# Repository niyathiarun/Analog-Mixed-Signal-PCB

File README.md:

# ⚙️ Analog–Mixed Signal PCB Project  

## 🧠 Project Overview  
This project focuses on designing and implementing a **mixed-signal printed circuit board (PCB)** that integrates both **analog** and **digital** subsystems on a single platform.  
The design features an **ATmega8L microcontroller** as the digital processing unit and an **operational amplifier (Op-Amp)** for analog signal conditioning.  

This project demonstrates key aspects of **analog–digital interfacing**, **signal conditioning**, **noise isolation**, and **mixed-signal PCB design principles**.  
All schematics, layouts, and fabrication outputs were created using **KiCad EDA**.

---

## 🎯 Objectives  

- To design and simulate a **mixed-signal circuit** combining analog and digital components.  
- To interface an **Op-Amp**-based analog conditioning circuit with a **microcontroller ADC**.  
- To implement effective **ground separation and power filtering** for signal integrity.  
- To generate **Gerber and drill files** for PCB fabrication and validation.  
- To gain hands-on experience in **mixed-signal design workflow** using KiCad.  

---

## 🧩 Key Features  

- **Microcontroller:** ATmega8L-8A (8-bit AVR MCU operating at 8 MHz)  
- **Analog Section:** Op-Amp-based amplifier and filter network  
- **Power Section:** 5V regulated supply with decoupling capacitors and ferrite bead  
- **Ground Planes:** Independent **GNDA** (Analog Ground) and **GNDD** (Digital Ground)  
- **Signal Interface:** Audio connector for analog input/output  
- **Design Tool:** KiCad 9.0.3  
- **Layers:** Two-layer PCB  
- **Fabrication Output:** Gerber and Drill files ready for manufacturing  

---

## 🧠 Circuit Explanation  

### 🔸 1. ATmega8L Microcontroller Section  
- Serves as the **digital control and processing unit**.  
- Reads analog signals from the op-amp through its **ADC pins**.  
- Capable of further processing, control, or display applications.  
- Decoupling capacitors are placed near **VCC** and **AVCC** pins to ensure stable ADC readings.  

### 🔸 2. Op-Amp Signal Conditioning Section  
- Amplifies and filters analog signals before feeding them into the ADC.  
- Provides clean and accurate analog voltages for digital conversion.  
- Includes RC filtering for stability and noise suppression.  
- Powered by the same 5V line as the MCU, isolated using ferrite bead and bypass capacitors.  

### 🔸 3. Power & Ground Separation  
- Power input through a **5V regulated line**.  
- **Ferrite bead** isolates analog and digital power domains.  
- **GNDA** and **GNDD** connected through a single low-impedance point near the power input.  
- This reduces cross-domain noise coupling and ensures better ADC accuracy.  

---

## 📐 PCB Design Highlights  

| Aspect | Description |
|--------|--------------|
| **Board Type** | 2-layer PCB |
| **Track Width** | Optimized based on current requirements |
| **Via Usage** | Minimal, used only for signal transitions |
| **Placement** | Clear separation between analog and digital components |
| **Ground Strategy** | Split ground plane with a single-star connection |
| **Decoupling** | 0.1µF ceramic + 10µF electrolytic capacitors near power pins |
| **Design Checks** | Passed ERC and DRC validation in KiCad |

---

## 📂 Repository Structure  

Analog-Mixed-Signal-PCB/
│
├── Schematic/
│ └── mixed_signal_project.kicad_sch
├── schematic_preview.png
│
├── PCB_Design/
│ └── mixed_signal_project.kicad_pcb
│ └── pcb_layout.png
│
├── Fabrication_Files/
│ ├── Gerber/
│ └── Drill_Files/
│ └── Gerber_drill_layout.png
│
└── README.md

---

## 🧰 Tools and Components  

| Category | Details |
|-----------|----------|
| **EDA Software** | KiCad 9.0.3 |
| **Microcontroller** | ATmega8L-8A |
| **Operational Amplifier** | LM358 / LM741 |
| **Power Source** | 5V DC Regulated Input |
| **Passive Components** | Resistors, capacitors, ferrite bead |
| **Connector** | Audio Jack (Analog I/O) |
| **Capacitors** | 0.1µF (decoupling), 10µF (filtering) |

---

## ⚡ Fabrication Notes  

- **Track Width:** 0.25 mm  
- **Clearance:** 0.2 mm  
- **Hole Diameter:** 0.8 mm  
- **Silkscreen:** Includes all reference designators and pin numbers  
- **Gerber Verification:** Done using Gerber Viewer before upload  
- **Board Type:** Standard FR-4 substrate, 1.6 mm thickness  

---

## 📈 Design Validation  

- ✅ **ERC (Electrical Rules Check):** No unconnected or shorted nets  
- ✅ **DRC (Design Rules Check):** Fully passed in KiCad  
- ✅ **Gerber Verification:** Verified visually for alignment and polarity   

---

## 🧩 Applications  

This mixed-signal PCB design has a wide range of **educational and industrial applications**, such as:  

- 🎛️ **Sensor Interface Systems** – conditioning analog sensor outputs before ADC conversion.  
- 🎚️ **Data Acquisition Systems** – capturing analog signals for processing in microcontrollers.  
- 🔊 **Audio Signal Processing** – amplifying and filtering low-level audio inputs.  
- 🧮 **Embedded Control Units** – combining analog feedback with digital decision logic.  
- 🧠 **Learning Platform** – for understanding mixed-signal PCB layout techniques.  

---

## 🧩 Learning Outcomes  

- Designed a **mixed-signal circuit** with analog–digital coexistence.  
- Implemented **noise isolation** and **power decoupling** techniques.  
- Created a **fabrication-ready PCB** with Gerber and drill files.  
- Practiced **KiCad design workflow** — schematic → layout → Gerber.  
- Gained insight into **real-world PCB manufacturing constraints**.  

---

## 🧑‍💻 Author  

**Niyathi Arun Kurthkoti**  
🎓 Electronics and Communication Engineering Student  
💡 Enthusiastic about Embedded Systems, PCB Design, and IoT  
📍 Passionate about creating real-world hardware solutions  

📫 *Connect with me:*  
[🔗 LinkedIn](www.linkedin.com/in/niyathiarun) 

---

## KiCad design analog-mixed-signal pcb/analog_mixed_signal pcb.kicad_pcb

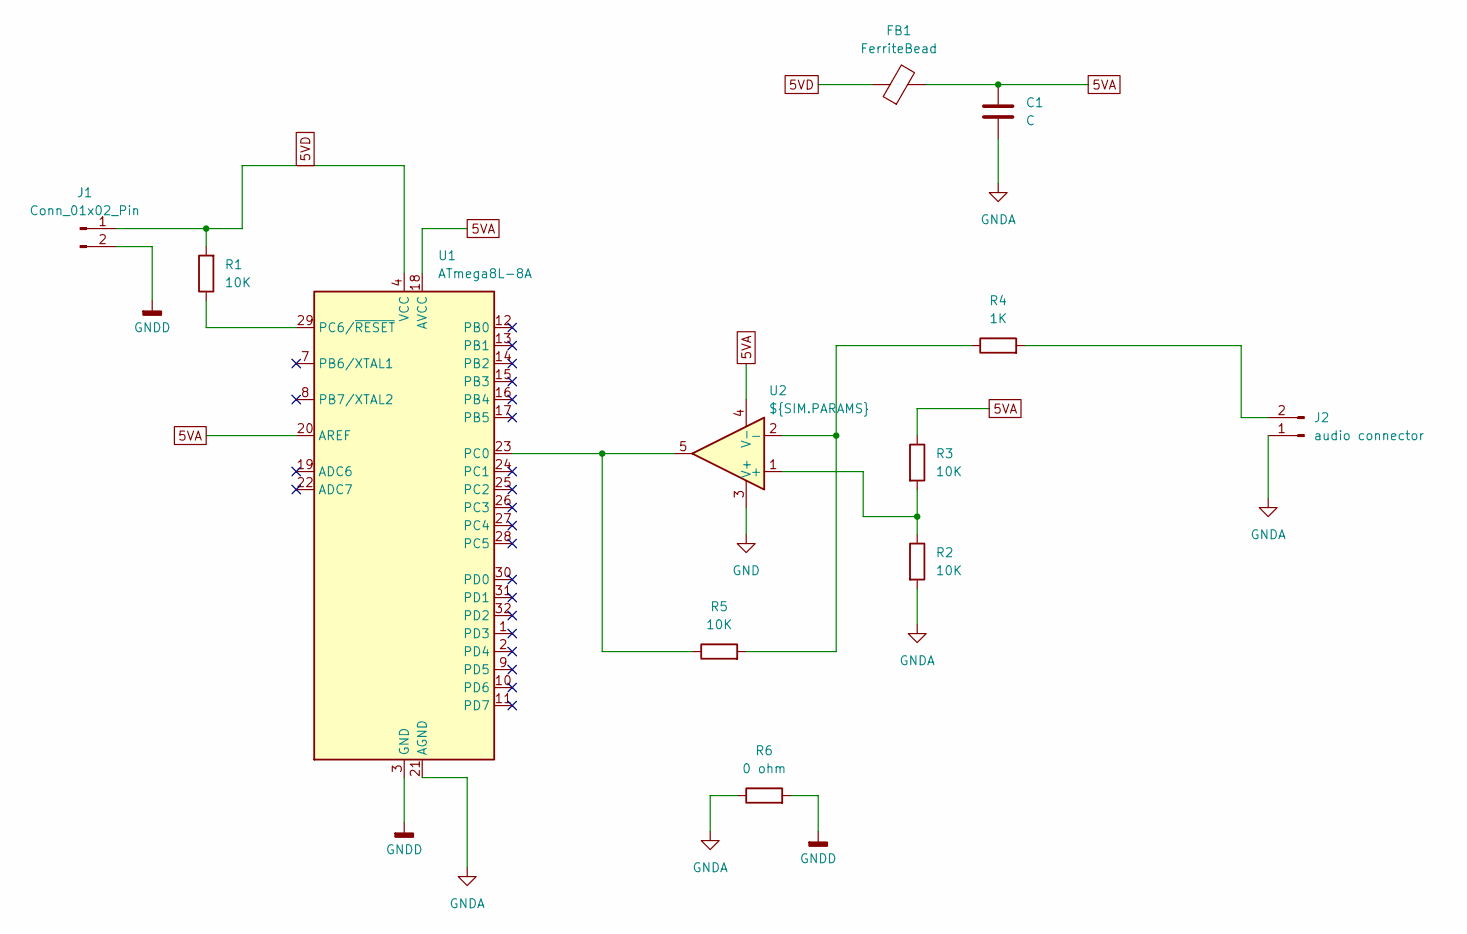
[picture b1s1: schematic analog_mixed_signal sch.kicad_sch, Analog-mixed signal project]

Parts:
C1: C; C_0603_1608Metric
FB1: FerriteBead; L_0603_1608Metric
J1: Conn_01x02_Pin; PinHeader_1x02_P2.54mm_Vertical
J2: audio connector; PinHeader_1x02_P2.54mm_Vertical
R1, R2, R3, R5: 10K; R_0603_1608Metric
R4: 1K; R_0603_1608Metric
R6: 0 ohm; R_0603_1608Metric
U1: ATmega8L-8A; TQFP-32_7x7mm_P0.8mm
U2: ${SIM.PARAMS}; SOIC-8_3.9x4.9mm_P1.27mm

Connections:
5VA: C1.1, FB1.2, R3.1, U1.18 (AVCC), U1.20 (AREF), U2.4 (V-)
5VD: FB1.1, J1.1, R1.2, U1.4 (VCC), U1.6 (VCC)
GND: U2.3 (V+)
GNDA: C1.2, J2.1, R2.2, R6.1, U1.21 (AGND)
GNDD: J1.2, R6.2, U1.3 (GND), U1.5 (GND)
unnamed: J2.2, R4.2
unnamed: R5.1, U1.23 (PC0), U2.5
unnamed: R1.1, U1.29 (PC6/~RESET)
unnamed: R2.1, R3.2, U2.1 (+)
unnamed: R4.1, R5.2, U2.2 (-)

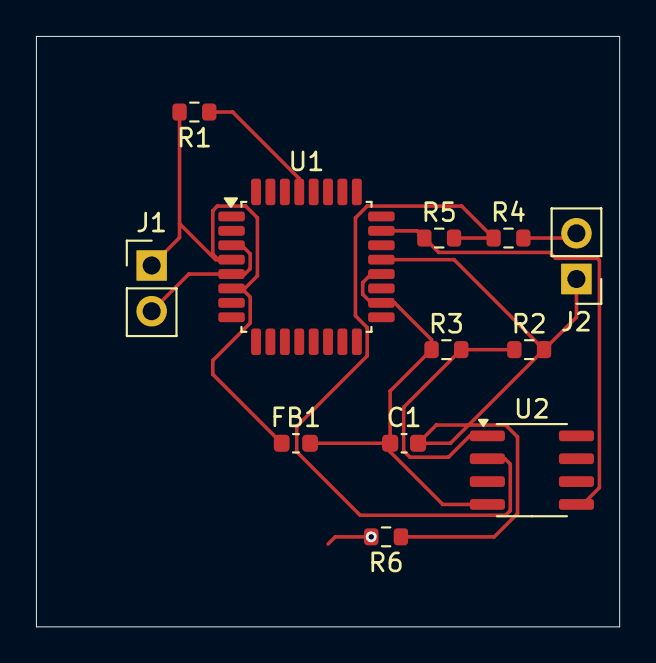
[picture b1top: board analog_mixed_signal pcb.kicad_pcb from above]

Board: 2 copper layers, 32.4 x 32.8 mm, 12 parts (0 on the bottom side), 9 nets.

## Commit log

2025-11-11 Add detailed README and complete KiCad project files for Analog–Mixed Signal PCB
    Expanded project details to provide a comprehensive overview, objectives, key features, circuit explanations, PCB design highlights, tools, fabrication notes, design validation, applications, and lea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
2025-11-11 updated all files
    includes schematic , PCB design , Gerber files with respective images
